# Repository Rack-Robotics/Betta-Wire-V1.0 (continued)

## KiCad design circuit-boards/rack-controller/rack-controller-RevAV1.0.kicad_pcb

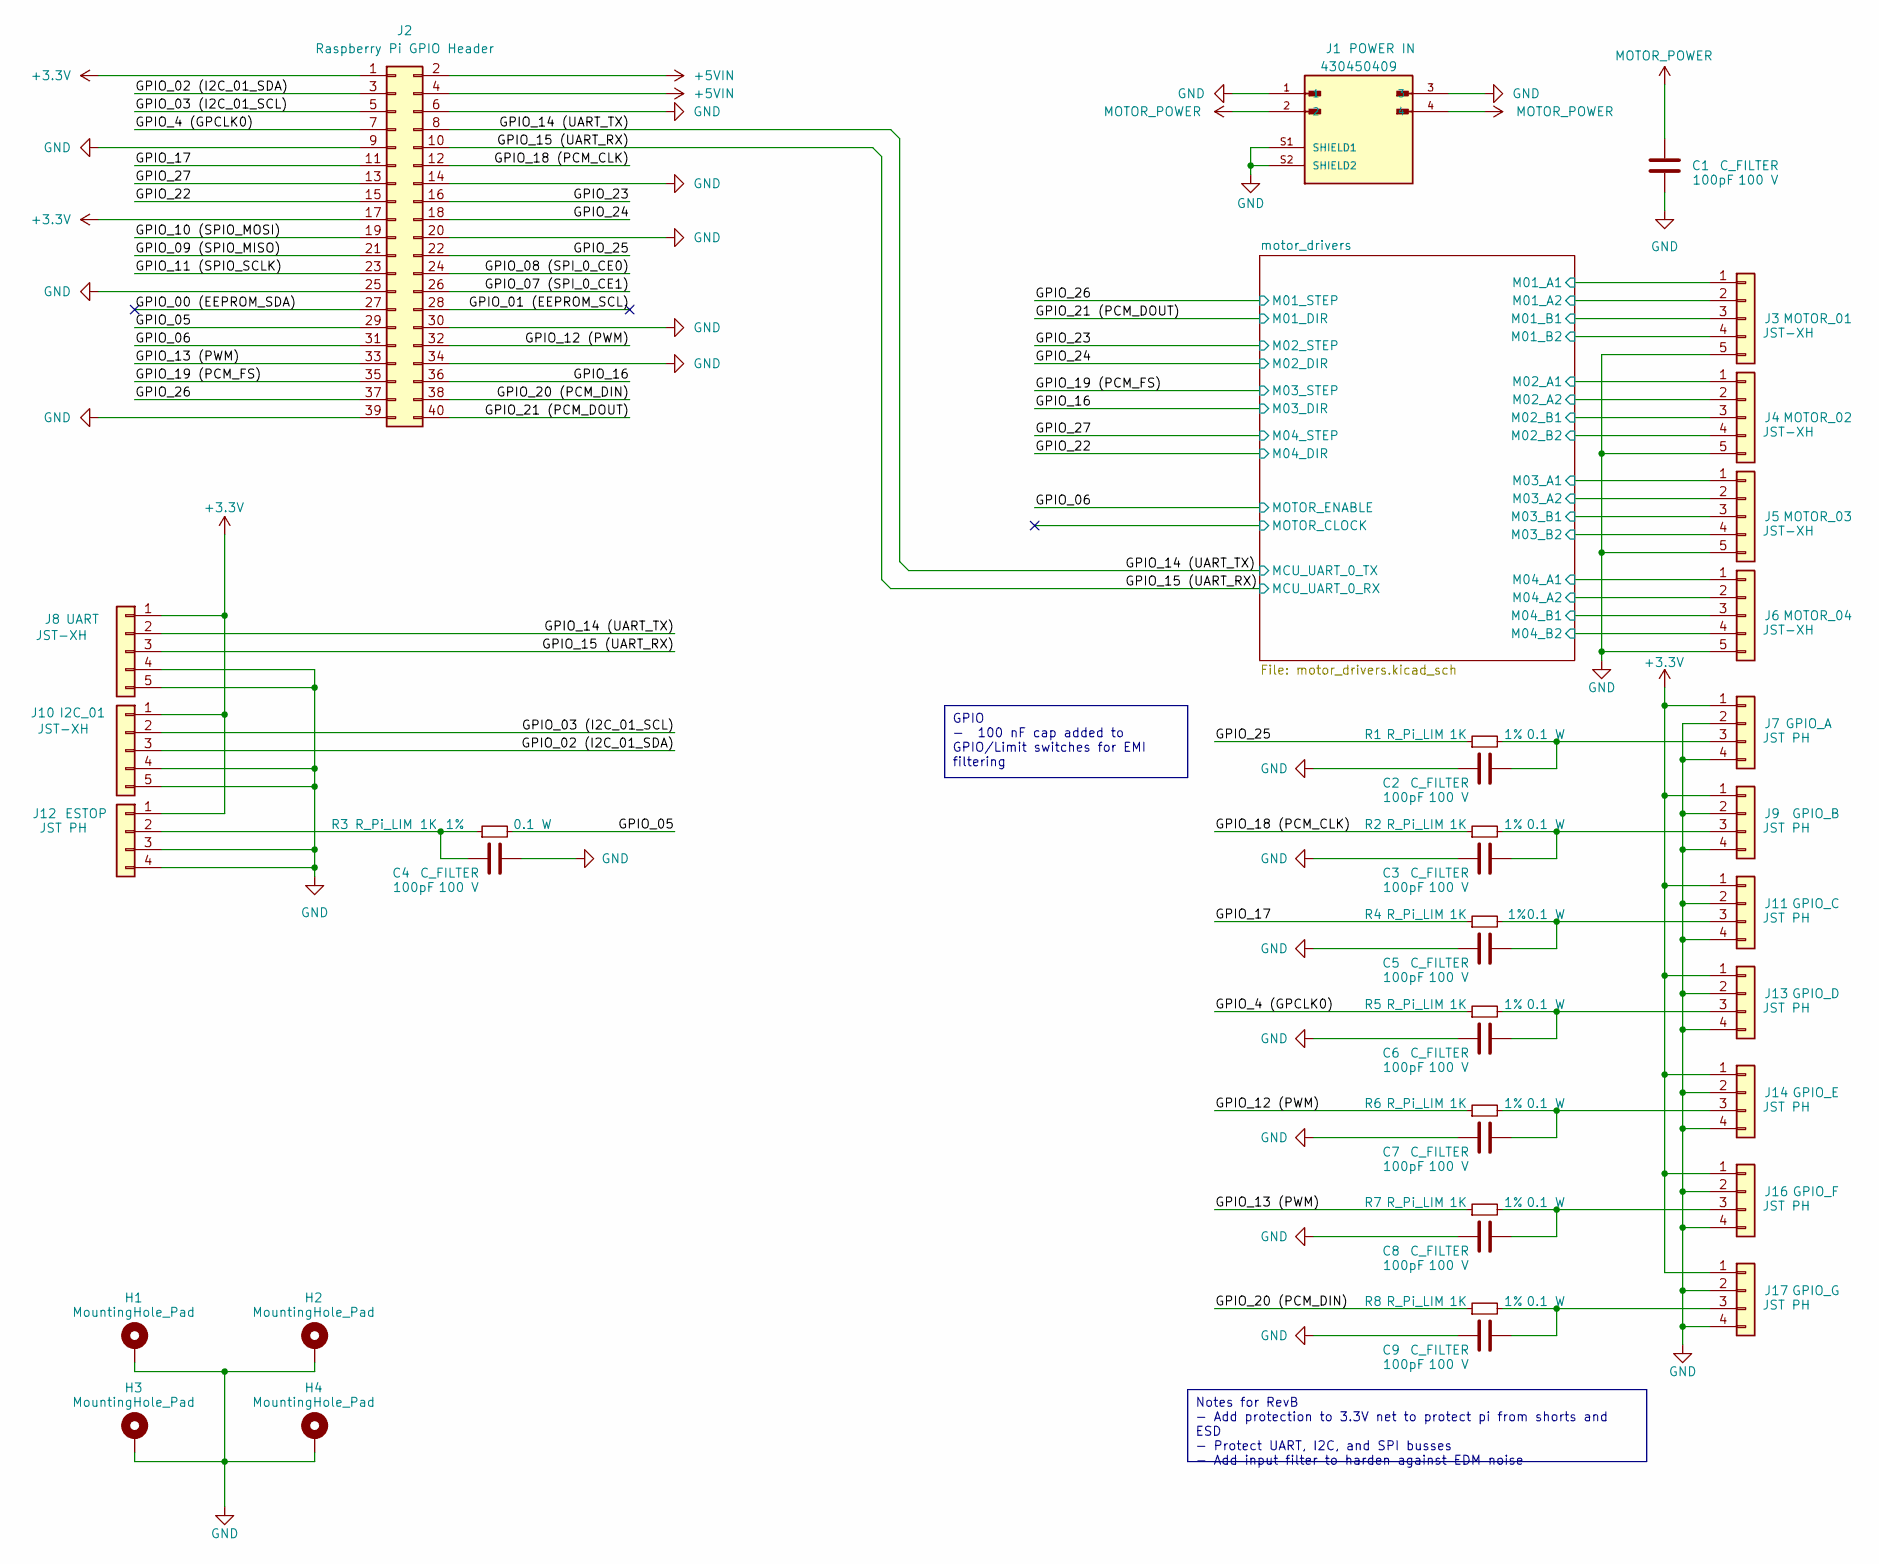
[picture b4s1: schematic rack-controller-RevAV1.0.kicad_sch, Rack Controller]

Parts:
C1, C2, C3, C4, C5, C6, C7, C8, C9: 100pF; C_0402_1005Metric; Voltage 100 V; Manufacturer# CC0402JRNPO0BN101; LCSC# C576700
H1, H2, H3, H4: MountingHole_Pad; MountingHole_3.2mm_M3_DIN965_Pad; Manufacturer# NULL; LCSC# NULL
J1: 430450409; MOLEX_430450409; Manufacturer# 0430450409; LCSC# C30602379
J2: Raspberry Pi GPIO Header; raspberrypi; Manufacturer# ESQ-120-23-T-D; LCSC# NULL
J3, J4, J5, J6, J8, J10: JST-XH; JST_XH_S4B-XH-SM4-TB_1x04-1MP_P2.50mm_Horizontal_custom; Manufacturer# S4B-XH-SM4-TB; LCSC# C161861
J7, J9, J11, J12, J13, J14, J16, J17: JST PH; JST_PH_S3B-PH-SM4-TB_1x03-1MP_P2.00mm_Horizontal_custom; Manufacturer# S3B-PH-SM4-TB; LCSC# C265101
R1, R2, R3, R4, R5, R6, R7, R8: 1K; R_0603_1608Metric; Tolerance 1%; Manufacturer# RC0603FR-071KL; LCSC# C22548

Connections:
+3.3V: J2.1, J2.17, J7.1, J8.1, J9.1, J10.1, J11.1, J12.1, J13.1, J14.1, J16.1, J17.1
+5VIN: J2.2, J2.4
/GPIO_00 (EEPROM_SDA): J2.27
/GPIO_01 (EEPROM_SCL): J2.28
/GPIO_02 (I2C_01_SDA): J2.3, J10.3
/GPIO_03 (I2C_01_SCL): J2.5, J10.2
/GPIO_4 (GPCLK0): J2.7, R5.1
/GPIO_05: J2.29, R3.2
/GPIO_06: J2.31; also elsewhere on the board
/GPIO_07 (SPI_0_CE1): J2.26
/GPIO_08 (SPI_0_CE0): J2.24
/GPIO_09 (SPIO_MISO): J2.21
/GPIO_10 (SPIO_MOSI): J2.19
/GPIO_11 (SPIO_SCLK): J2.23
/GPIO_12 (PWM): J2.32, R6.1
/GPIO_13 (PWM): J2.33, R7.1
/GPIO_14 (UART_TX): J2.8, J8.2; also elsewhere on the board
/GPIO_15 (UART_RX): J2.10, J8.3; also elsewhere on the board
/GPIO_16: J2.36; also elsewhere on the board
/GPIO_17: J2.11, R4.1
/GPIO_18 (PCM_CLK): J2.12, R2.1
/GPIO_19 (PCM_FS): J2.35; also elsewhere on the board
/GPIO_20 (PCM_DIN): J2.38, R8.1
/GPIO_21 (PCM_DOUT): J2.40; also elsewhere on the board
/GPIO_22: J2.15; also elsewhere on the board
/GPIO_23: J2.16; also elsewhere on the board
/GPIO_24: J2.18; also elsewhere on the board
/GPIO_25: J2.22, R1.1
/GPIO_26: J2.37; also elsewhere on the board
/GPIO_27: J2.13; also elsewhere on the board
/motor_drivers/M01_A1: J3.1; also elsewhere on the board
/motor_drivers/M01_A2: J3.2; also elsewhere on the board
/motor_drivers/M01_B1: J3.3; also elsewhere on the board
/motor_drivers/M01_B2: J3.4; also elsewhere on the board
/motor_drivers/M02_A1: J4.1; also elsewhere on the board
/motor_drivers/M02_A2: J4.2; also elsewhere on the board
/motor_drivers/M02_B1: J4.3; also elsewhere on the board
/motor_drivers/M02_B2: J4.4; also elsewhere on the board
/motor_drivers/M03_A1: J5.1; also elsewhere on the board
/motor_drivers/M03_A2: J5.2; also elsewhere on the board
/motor_drivers/M03_B1: J5.3; also elsewhere on the board
/motor_drivers/M03_B2: J5.4; also elsewhere on the board
/motor_drivers/M04_A1: J6.1; also elsewhere on the board
/motor_drivers/M04_A2: J6.2; also elsewhere on the board
/motor_drivers/M04_B1: J6.3; also elsewhere on the board
/motor_drivers/M04_B2: J6.4; also elsewhere on the board
GND: C1.1, C2.1, C3.1, C4.2, C5.1, C6.1, C7.1, C8.1, C9.1, H1.1, H2.1, H3.1, H4.1, J1.1, J1.3, J1.S1 (SHIELD1), J1.S2 (SHIELD2), J2.6, J2.9, J2.14, J2.20, J2.25, J2.30, J2.34, J2.39, J3.5, J4.5, J5.5, J6.5, J7.2, J7.4, J8.4, J8.5, J9.2, J9.4, J10.4, J10.5, J11.2, J11.4, J12.3, J12.4, J13.2, J13.4, J14.2, J14.4, J16.2, J16.4, J17.2, J17.4; also elsewhere on the board
MOTOR_POWER: C1.2, J1.2, J1.4; also elsewhere on the board
unnamed: C2.2, J7.3, R1.2
unnamed: C3.2, J9.3, R2.2
unnamed: C5.2, J11.3, R4.2
unnamed: C4.1, J12.2, R3.1
unnamed: C6.2, J13.3, R5.2
unnamed: C7.2, J14.3, R6.2
unnamed: C8.2, J16.3, R7.2
unnamed: C9.2, J17.3, R8.2

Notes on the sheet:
GPIO - 100 nF cap added to GPIO/Limit switches for EMI filtering
Notes for RevB - Add protection to 3.3V net to protect pi from shorts and ESD - Protect UART, I2C, and SPI busses - Add input filter to harden against EDM noise

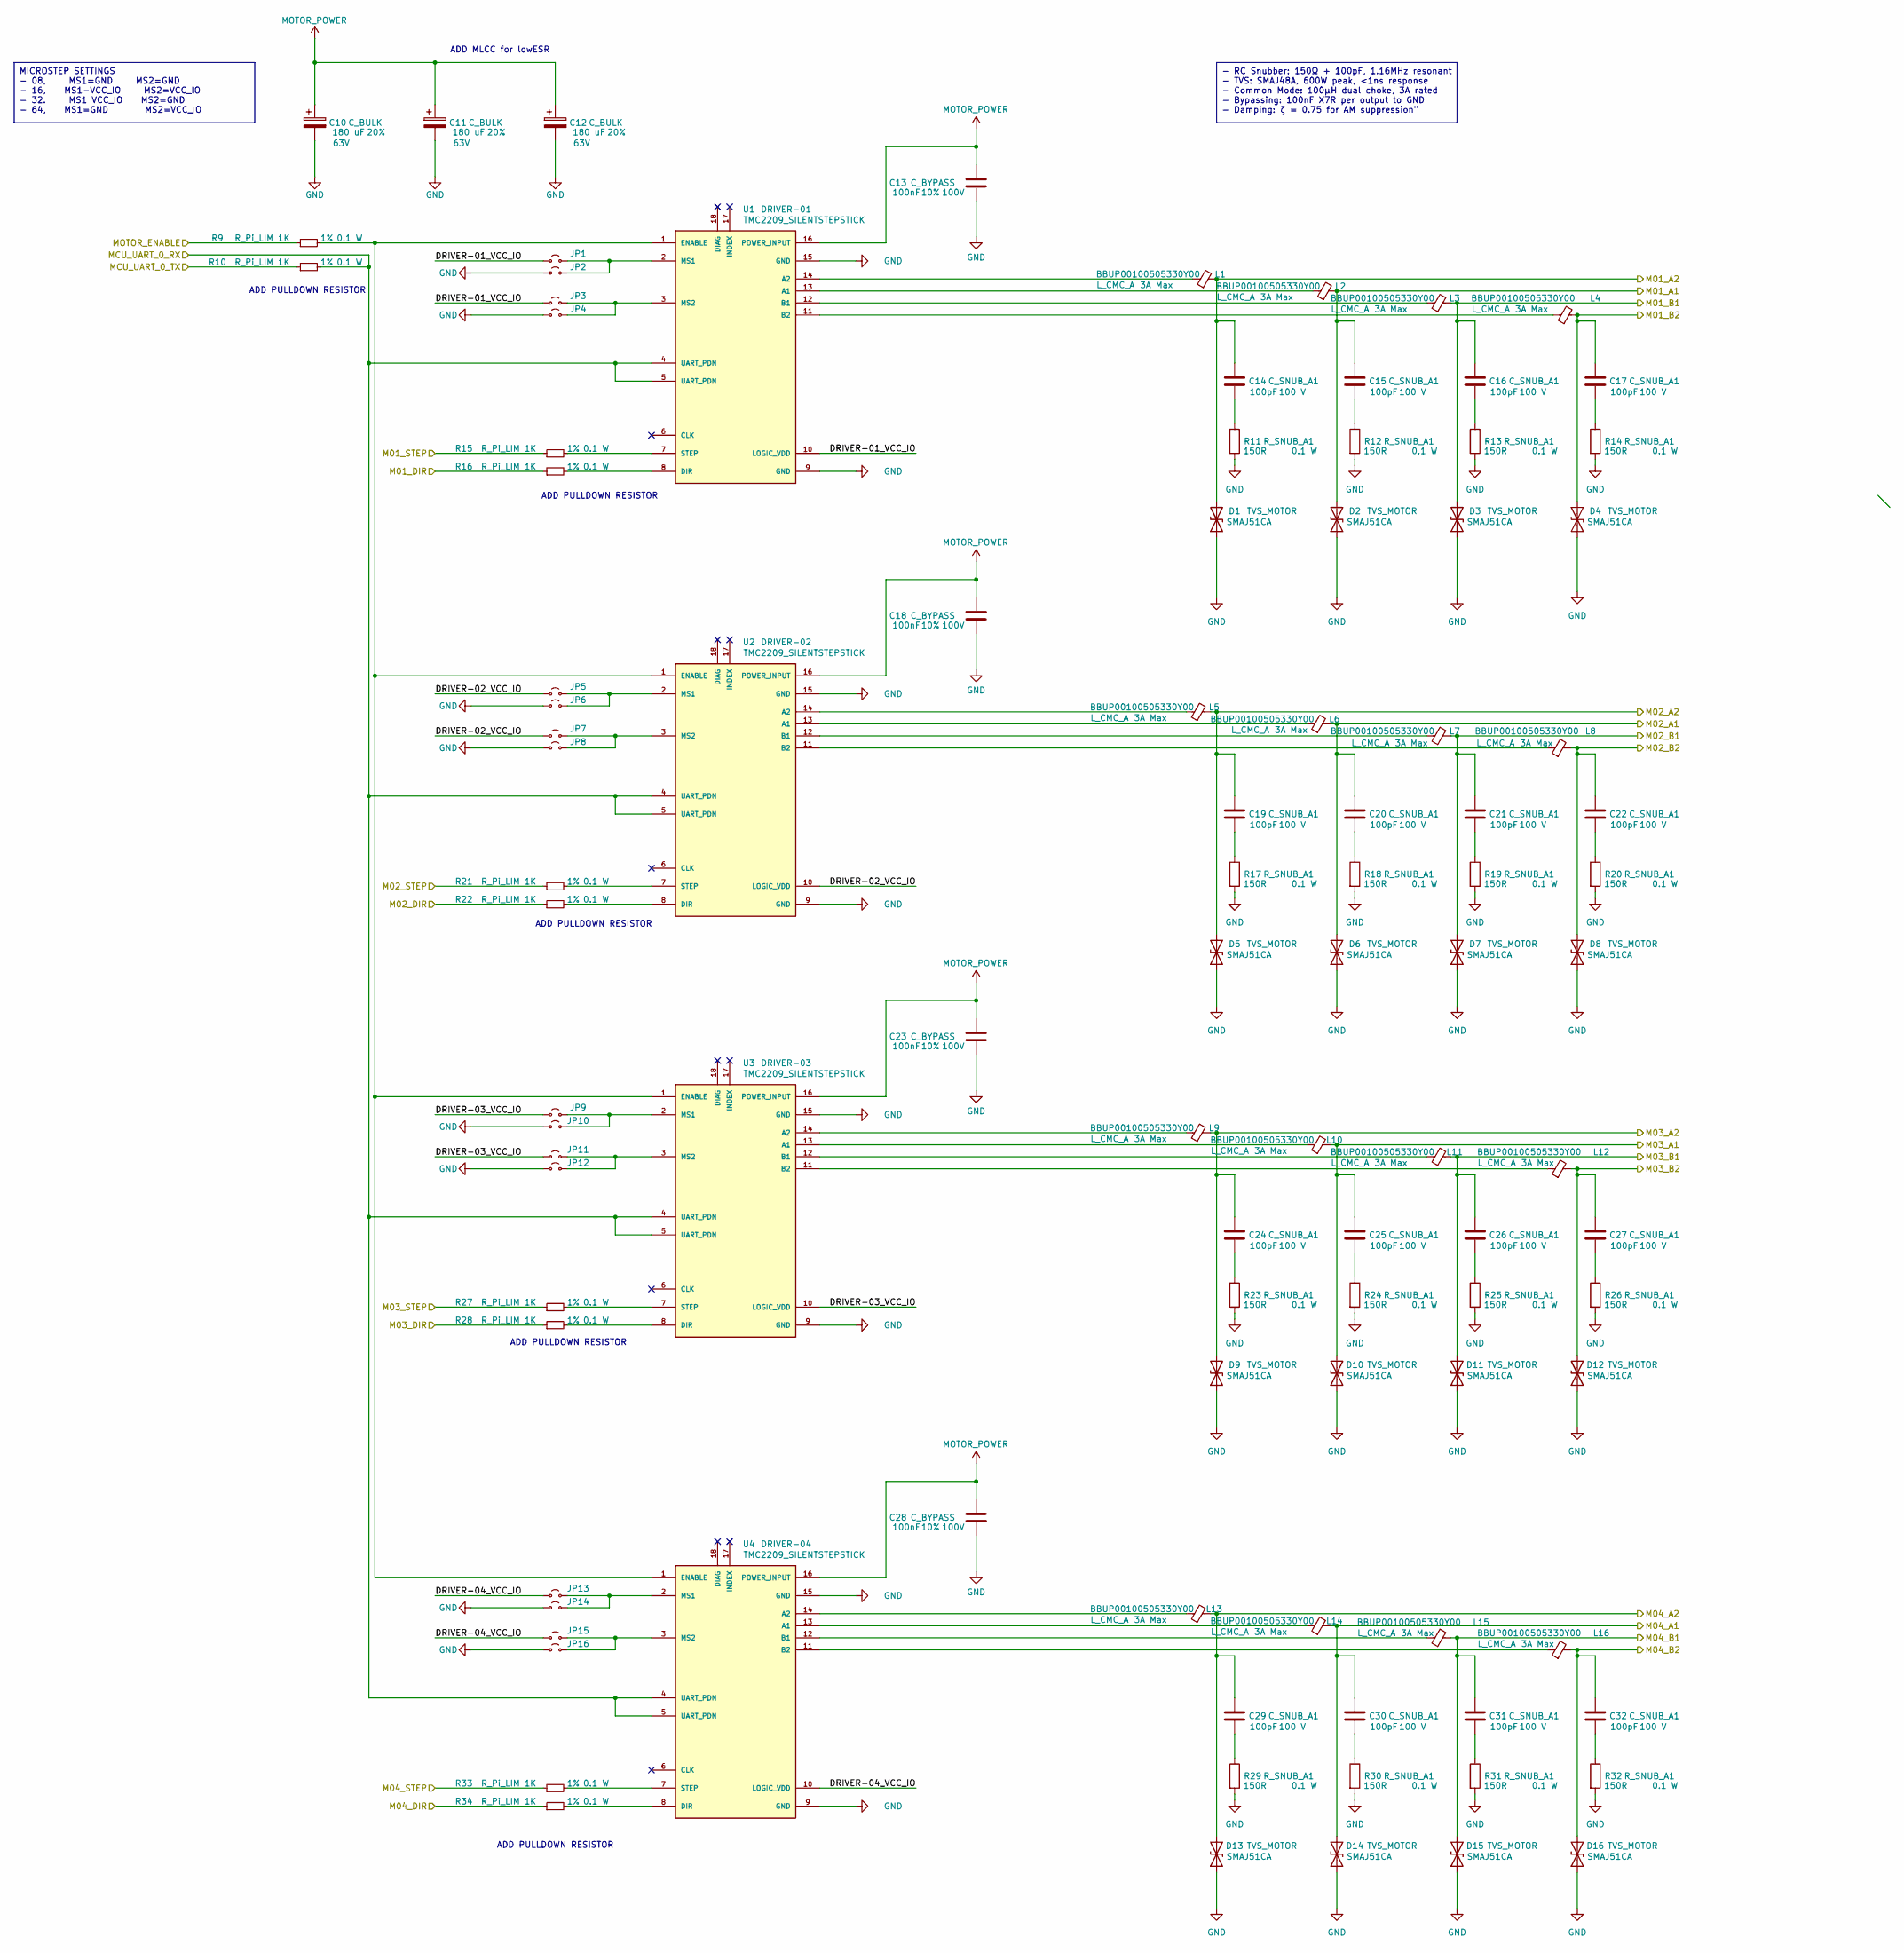
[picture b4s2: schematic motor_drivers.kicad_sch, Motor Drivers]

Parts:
C10, C11, C12: 180 uF; CP_Elec_10x10; Voltage 63V; Tolerance 20%; Manufacturer# A785MW187M1JLAS013; LCSC# NULL
C13, C18, C23, C28: 100nF; C_0603_1608Metric; Voltage 100V; Tolerance 10%; Manufacturer# CC0603KRX7R0BB104; LCSC# C113803
C14, C15, C16, C17, C19, C20, C21, C22, C24, C25, C26, C27, C29, C30, C31, C32: 100pF; C_0402_1005Metric; Voltage 100 V; Manufacturer# CC0402JRNPO0BN101; LCSC# C576700
D1, D2, D3, D4, D5, D6, D7, D8, D9, D10, D11, D12, D13, D14, D15, D16: SMAJ51CA; D_SMA; Manufacturer# SMAJ60CA-13-F; LCSC# C135003
JP1, JP2, JP3, JP4, JP5, JP6, JP7, JP8, JP9, JP10, JP11, JP12, JP13, JP14, JP15, JP16: NULL; SolderJumper-2_P1mm_UnBridged_Pad1.6x1.6mm; Manufacturer# NULL; LCSC# NULL
L1, L2, L3, L4, L5, L6, L7, L8, L9, L10, L11, L12, L13, L14, L15, L16: BBUP00100505330Y00; L_0402_1005Metric; Manufacturer# BLM15AX100SN1D; LCSC# C668299
R9, R10, R15, R16, R21, R22, R27, R28, R33, R34: 1K; R_0603_1608Metric; Tolerance 1%; Manufacturer# RC0603FR-071KL; LCSC# C22548
R11, R12, R13, R14, R17, R18, R19, R20, R23, R24, R25, R26, R29, R30, R31, R32: 150R; R_0603_1608Metric; Tolerance 1%; Manufacturer# RC0603FR-07150RL; LCSC# C114608
U1, U2, U3, U4: TMC2209_SILENTSTEPSTICK; BTT_TMC2209_V1.3; Manufacturer# TMC2209_V1.3; LCSC# NULL

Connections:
/GPIO_06: R9.1; also elsewhere on the board
/GPIO_14 (UART_TX): R10.1; also elsewhere on the board
/GPIO_15 (UART_RX): R10.2, U1.4 (UART_PDN), U1.5 (UART_PDN), U2.4 (UART_PDN), U2.5 (UART_PDN), U3.4 (UART_PDN), U3.5 (UART_PDN), U4.4 (UART_PDN), U4.5 (UART_PDN); also elsewhere on the board
/GPIO_16: R28.1; also elsewhere on the board
/GPIO_19 (PCM_FS): R27.1; also elsewhere on the board
/GPIO_21 (PCM_DOUT): R16.1; also elsewhere on the board
/GPIO_22: R34.1; also elsewhere on the board
/GPIO_23: R21.1; also elsewhere on the board
/GPIO_24: R22.1; also elsewhere on the board
/GPIO_26: R15.1; also elsewhere on the board
/GPIO_27: R33.1; also elsewhere on the board
/motor_drivers/DRIVER-01_VCC_IO: JP1.1 (A), JP3.1 (A), U1.10 (LOGIC_VDD)
/motor_drivers/DRIVER-02_VCC_IO: JP5.1 (A), JP7.1 (A), U2.10 (LOGIC_VDD)
/motor_drivers/DRIVER-03_VCC_IO: JP9.1 (A), JP11.1 (A), U3.10 (LOGIC_VDD)
/motor_drivers/DRIVER-04_VCC_IO: JP13.1 (A), JP15.1 (A), U4.10 (LOGIC_VDD)
/motor_drivers/M01_A1: C15.1, D2.2 (A2), L2.2; also elsewhere on the board
/motor_drivers/M01_A2: C14.1, D1.2 (A2), L1.2; also elsewhere on the board
/motor_drivers/M01_B1: C16.1, D3.2 (A2), L3.2; also elsewhere on the board
/motor_drivers/M01_B2: C17.1, D4.2 (A2), L4.2; also elsewhere on the board
/motor_drivers/M02_A1: C20.1, D6.2 (A2), L6.2; also elsewhere on the board
/motor_drivers/M02_A2: C19.1, D5.2 (A2), L5.2; also elsewhere on the board
/motor_drivers/M02_B1: C21.1, D7.2 (A2), L7.2; also elsewhere on the board
/motor_drivers/M02_B2: C22.1, D8.2 (A2), L8.2; also elsewhere on the board
/motor_drivers/M03_A1: C25.1, D10.2 (A2), L10.2; also elsewhere on the board
/motor_drivers/M03_A2: C24.1, D9.2 (A2), L9.2; also elsewhere on the board
/motor_drivers/M03_B1: C26.1, D11.2 (A2), L11.2; also elsewhere on the board
/motor_drivers/M03_B2: C27.1, D12.2 (A2), L12.2; also elsewhere on the board
/motor_drivers/M04_A1: C30.1, D14.2 (A2), L14.2; also elsewhere on the board
/motor_drivers/M04_A2: C29.1, D13.2 (A2), L13.2; also elsewhere on the board
/motor_drivers/M04_B1: C31.1, D15.2 (A2), L15.2; also elsewhere on the board
/motor_drivers/M04_B2: C32.1, D16.2 (A2), L16.2; also elsewhere on the board
GND: C10.2, C11.2, C12.2, C13.2, C18.2, C23.2, C28.2, D1.1 (A1), D2.1 (A1), D3.1 (A1), D4.1 (A1), D5.1 (A1), D6.1 (A1), D7.1 (A1), D8.1 (A1), D9.1 (A1), D10.1 (A1), D11.1 (A1), D12.1 (A1), D13.1 (A1), D14.1 (A1), D15.1 (A1), D16.1 (A1), JP2.1 (A), JP4.1 (A), JP6.1 (A), JP8.1 (A), JP10.1 (A), JP12.1 (A), JP14.1 (A), JP16.1 (A), R11.2, R12.2, R13.2, R14.2, R17.2, R18.2, R19.2, R20.2, R23.2, R24.2, R25.2, R26.2, R29.2, R30.2, R31.2, R32.2, U1.9 (GND), U1.15 (GND), U2.9 (GND), U2.15 (GND), U3.9 (GND), U3.15 (GND), U4.9 (GND), U4.15 (GND); also elsewhere on the board
MOTOR_POWER: C10.1, C11.1, C12.1, C13.1, C18.1, C23.1, C28.1, U1.16 (POWER_INPUT), U2.16 (POWER_INPUT), U3.16 (POWER_INPUT), U4.16 (POWER_INPUT); also elsewhere on the board
unnamed: C14.2, R11.1
unnamed: C15.2, R12.1
unnamed: C16.2, R13.1
unnamed: C17.2, R14.1
unnamed: C19.2, R17.1
unnamed: C20.2, R18.1
unnamed: C21.2, R19.1
unnamed: C22.2, R20.1
unnamed: C24.2, R23.1
unnamed: C25.2, R24.1
unnamed: C26.2, R25.1
unnamed: C27.2, R26.1
unnamed: C29.2, R29.1
unnamed: C30.2, R30.1
unnamed: C31.2, R31.1
unnamed: C32.2, R32.1
unnamed: JP1.2 (B), JP2.2 (B), U1.2 (MS1)
unnamed: JP3.2 (B), JP4.2 (B), U1.3 (MS2)
unnamed: JP5.2 (B), JP6.2 (B), U2.2 (MS1)
unnamed: JP7.2 (B), JP8.2 (B), U2.3 (MS2)
unnamed: JP9.2 (B), JP10.2 (B), U3.2 (MS1)
unnamed: JP11.2 (B), JP12.2 (B), U3.3 (MS2)
unnamed: JP13.2 (B), JP14.2 (B), U4.2 (MS1)
unnamed: JP15.2 (B), JP16.2 (B), U4.3 (MS2)
unnamed: L2.1, U1.13 (A1)
unnamed: L1.1, U1.14 (A2)
unnamed: L3.1, U1.12 (B1)
unnamed: L4.1, U1.11 (B2)
unnamed: R16.2, U1.8 (DIR)
unnamed: R9.2, U1.1 (ENABLE), U2.1 (ENABLE), U3.1 (ENABLE), U4.1 (ENABLE)
unnamed: R15.2, U1.7 (STEP)
unnamed: L6.1, U2.13 (A1)
unnamed: L5.1, U2.14 (A2)
unnamed: L7.1, U2.12 (B1)
unnamed: L8.1, U2.11 (B2)
unnamed: R22.2, U2.8 (DIR)
unnamed: R21.2, U2.7 (STEP)
unnamed: L10.1, U3.13 (A1)
unnamed: L9.1, U3.14 (A2)
unnamed: L11.1, U3.12 (B1)
unnamed: L12.1, U3.11 (B2)
unnamed: R28.2, U3.8 (DIR)
unnamed: R27.2, U3.7 (STEP)
unnamed: L14.1, U4.13 (A1)
unnamed: L13.1, U4.14 (A2)
unnamed: L15.1, U4.12 (B1)
unnamed: L16.1, U4.11 (B2)
unnamed: R34.2, U4.8 (DIR)
unnamed: R33.2, U4.7 (STEP)

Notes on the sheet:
- RC Snubber: 150Ω + 100pF, 1.16MHz resonant - TVS: SMAJ48A, 600W peak, <1ns response - Common Mode: 100µH dual choke, 3A rated - Bypassing: 100nF X7R per output to GND - Damping: ζ = 0.75 for AM suppression"
MICROSTEP SETTINGS - 08, MS1=GND MS2=GND - 16, MS1-VCC_IO MS2=VCC_IO - 32. MS1 VCC_IO MS2=GND - 64, MS1=GND MS2=VCC_IO
ADD PULLDOWN RESISTOR
ADD MLCC for lowESR

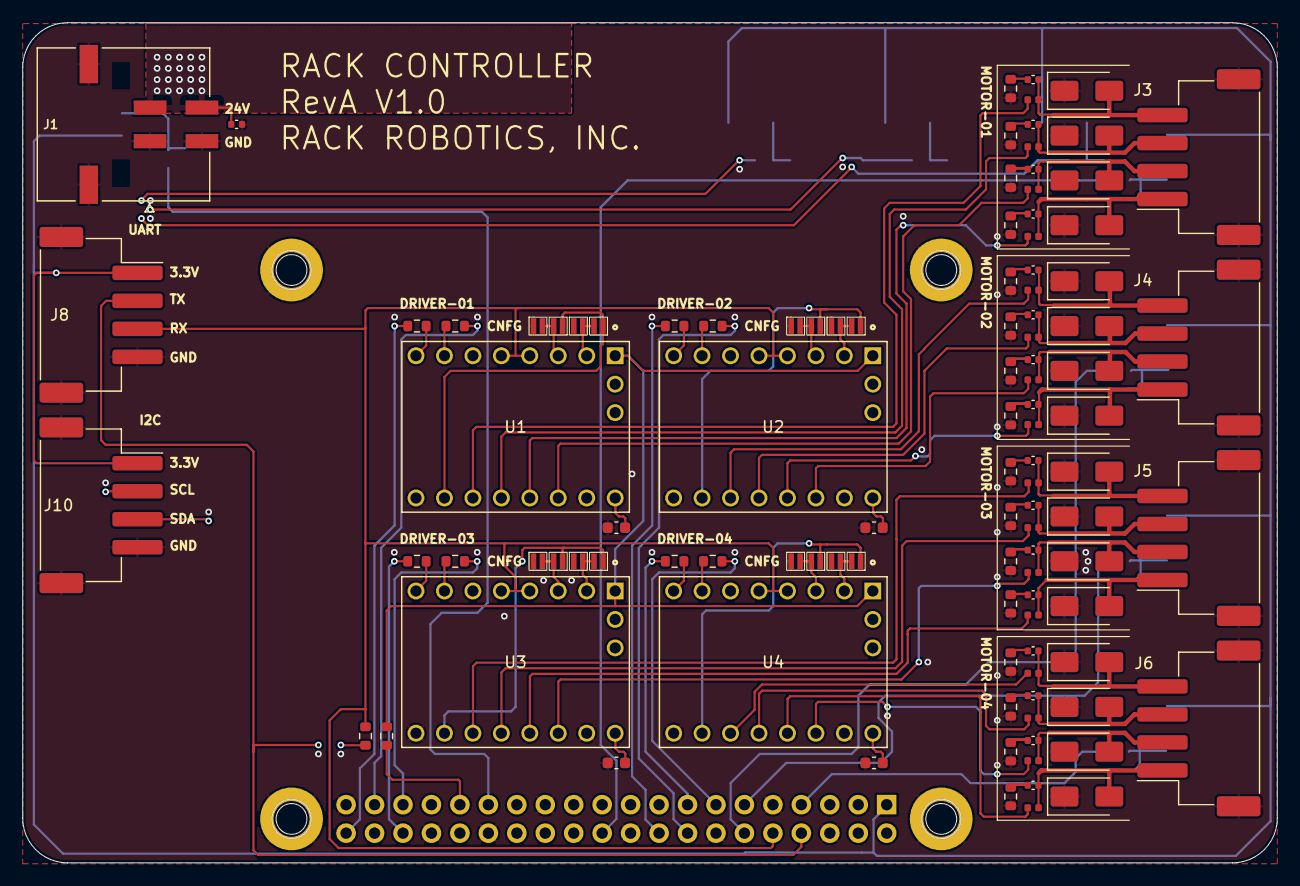
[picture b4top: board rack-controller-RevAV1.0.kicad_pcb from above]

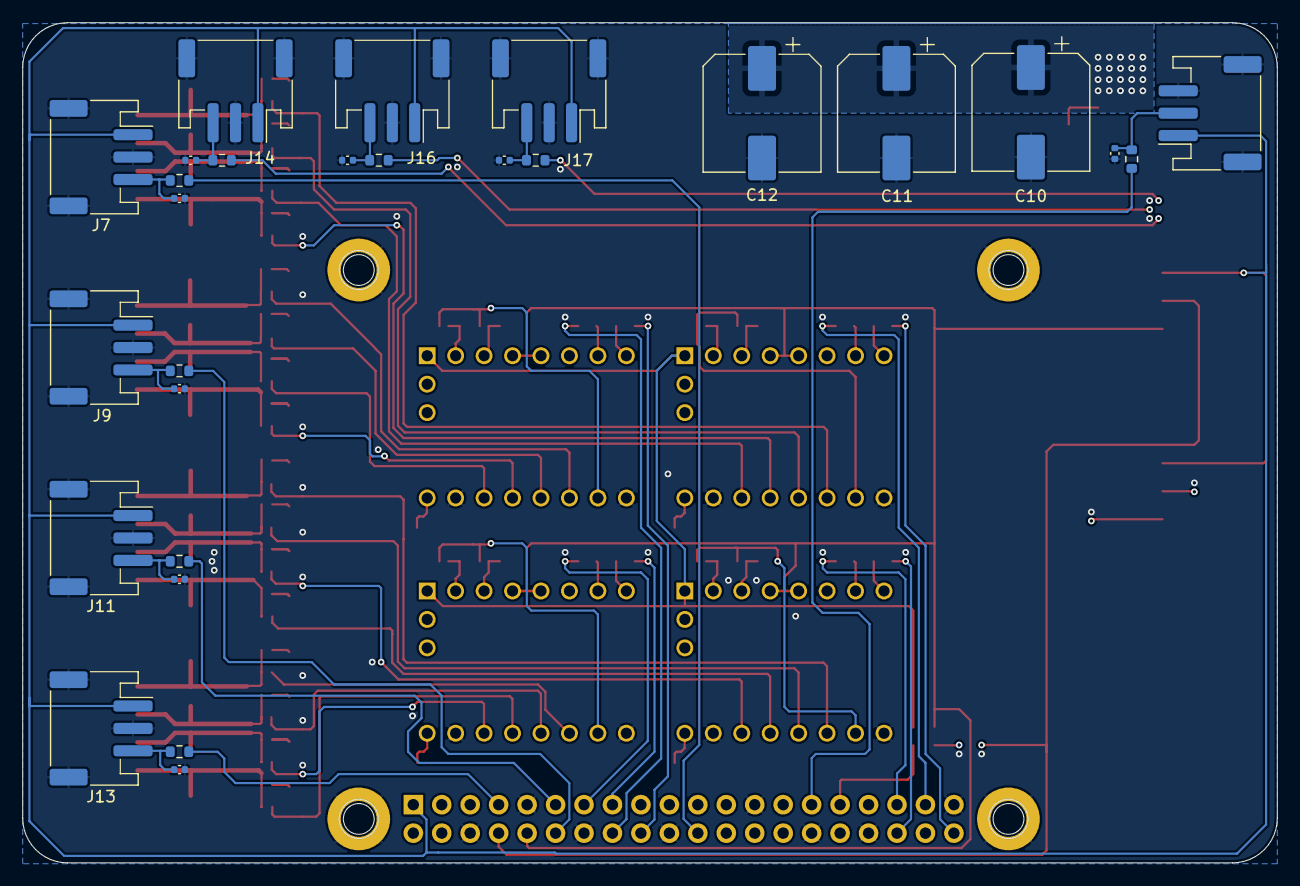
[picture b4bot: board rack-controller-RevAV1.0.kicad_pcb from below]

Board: 6 copper layers, 112.0 x 75.0 mm, 139 parts (27 on the bottom side), 102 nets.

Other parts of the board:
RP4: Raspberry_Pi; raspberrypi-outline

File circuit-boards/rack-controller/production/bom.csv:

Designator,Footprint,Quantity,Value,LCSC Part #
"C1, C14, C15, C16, C17, C19, C2, C20, C21, C22, C24, C25, C26, C27, C29, C3, C30, C31, C32, C4, C5, C6, C7, C8, C9",0402,25,100pF,
"C10, C11, C12",CP_Elec_10x10,3,180 uF,
"C13, C18, C23, C28",0603,4,100nF,
"D1, D10, D11, D12, D13, D14, D15, D16, D2, D3, D4, D5, D6, D7, D8, D9",D_SMA,16,SMAJ51CA,
J1,MOLEX_430450409,1,430450409,
"J10, J3, J4, J5, J6, J8",JST_XH_S4B-XH-SM4-TB_1x04-1MP_P2.50mm_Horizontal_custom,6,JST-XH,
"J11, J12, J13, J14, J16, J17, J7, J9",JST_PH_S3B-PH-SM4-TB_1x03-1MP_P2.00mm_Horizontal_custom,8,JST PH,
J2,raspberrypi,1,Raspberry Pi GPIO Header,
"JP1, JP10, JP11, JP12, JP13, JP14, JP15, JP16, JP2, JP3, JP4, JP5, JP6, JP7, JP8, JP9",SolderJumper-2_P1mm_UnBridged_Pad1.6x1.6mm,16,NULL,
"L1, L10, L11, L12, L13, L14, L15, L16, L2, L3, L4, L5, L6, L7, L8, L9",0402,16,BBUP00100505330Y00,
"R1, R10, R15, R16, R2, R21, R22, R27, R28, R3, R33, R34, R4, R5, R6, R7, R8, R9",0603,18,1K,
"R11, R12, R13, R14, R17, R18, R19, R20, R23, R24, R25, R26, R29, R30, R31, R32",0603,16,150R,
"U1, U2, U3, U4",BTT_TMC2209_V1.3,4,TMC2209_SILENTSTEPSTICK,

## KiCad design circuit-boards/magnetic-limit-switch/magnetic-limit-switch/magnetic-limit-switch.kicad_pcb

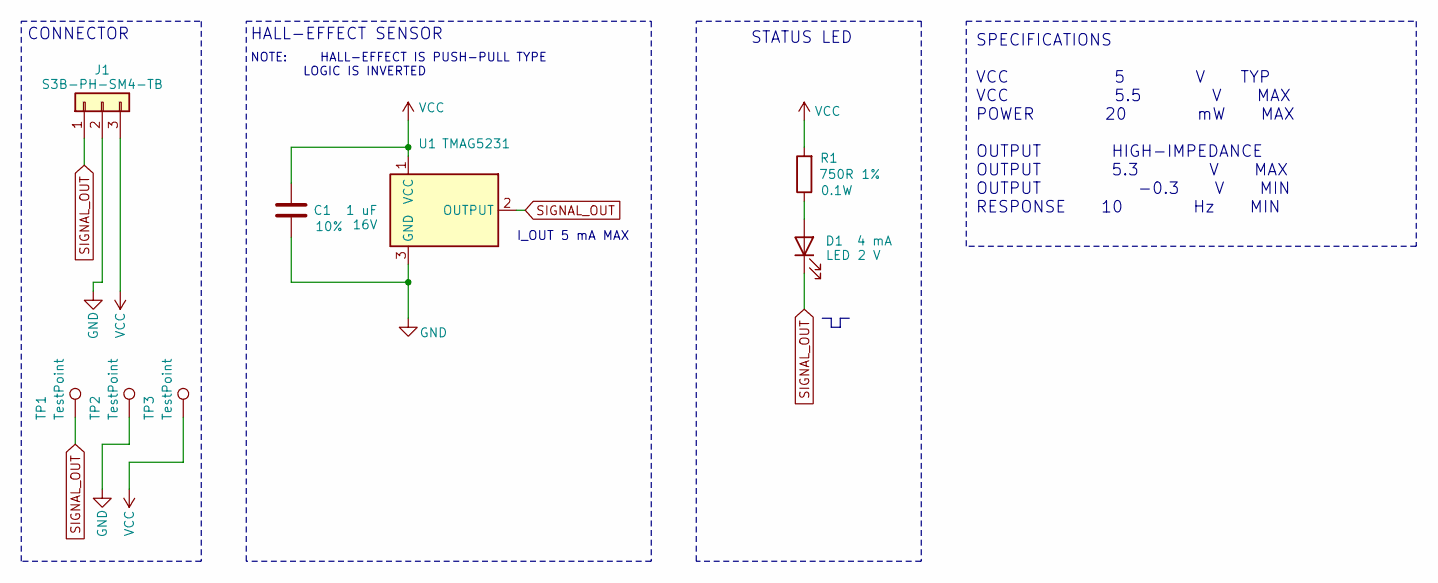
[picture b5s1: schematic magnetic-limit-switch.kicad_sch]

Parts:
C1: 1 uF; C_0603_1608Metric; Tolerance 10%; Manufacterer# CC0603KRX7R7BB105; LCSC Part # C106248
D1: LED; LED_0603_1608Metric; Manufacterer# LTST-C193KFKT-5A; LCSC Part # C284922
J1: S3B-PH-SM4-TB; JST_PH_S3B-PH-SM4-TB_1x03-1MP_P2.00mm_Horizontal; Manufacterer# S3B-PH-SM4-TB; LCSC Part # NULL
R1: 750R; R_0603_1608Metric; Tolerance 1%; Manufacterer# RC0603FR-07750RL; LCSC Part # C114635
TP1, TP2, TP3: TestPoint; TestPoint_Pad_1.0x1.0mm; Manufacterer# NULL; LCSC Part # NULL
U1: TMAG5231; SOT-23-3; Manufacterer# TMAG5231A2DQDBZR; LCSC Part # NULL

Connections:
GND: C1.1, J1.2, TP2.1, U1.3 (GND)
unnamed: D1.2 (A), R1.1
SIGNAL_OUT: D1.1 (K), J1.1, TP1.1, U1.2 (OUTPUT)
VCC: C1.2, J1.3, R1.2, TP3.1, U1.1 (VCC)

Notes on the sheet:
NOTE: HALL-EFFECT IS PUSH-PULL TYPE LOGIC IS INVERTED
CONNECTOR
HALL-EFFECT SENSOR
STATUS LED
SPECIFICATIONS VCC 5 V TYP VCC 5.5 V MAX POWER 20 mW MAX OUTPUT HIGH-IMPEDANCE OUTPUT 5.3 V MAX OUTPUT -0.3 V MIN RESPONSE 10 Hz MIN
I_OUT 5 mA MAX

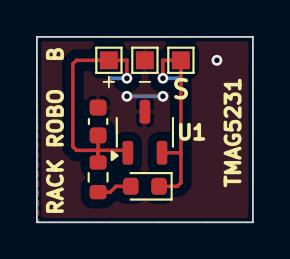
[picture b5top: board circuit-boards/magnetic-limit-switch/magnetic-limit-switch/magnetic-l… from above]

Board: 2 copper layers, 12.0 x 10.3 mm, 8 parts (1 on the bottom side), 4 nets.

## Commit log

2024-06-03 Update README.md license
2024-06-03 uploaded license
2024-06-03 added CAD, firmware, & images
2024-06-03 added image of tools
2024-06-03 added images of motor banks and e-box
2024-06-04 removed RevA files from RevB fork, modified designdecisions.md
2024-06-16 improved design decisions
2024-06-26 added requirements doc
2024-06-26 updated requirements
2024-06-26 added requirements for closed-loop feedrate control
2024-06-26 fixed typo in requirements
2024-06-29 Update betta-wire-v1.0-revb-requirements.md with analog voltage
2024-08-02 updated wire EDM toolhead sections
2024-08-15 updated design decisions
2024-08-15 updated requirements and organized into folder
2024-08-19 updated requirements with wire tension specs
2024-08-21 IP68 limit switch
2024-08-21 updated constraints to 0.2 mm diameter wire
2024-10-21 Proofreading
    Cleaned up formatting. Fixed a few spelling errors. Removed a few unnecessary words. Added further description. Added a link where appropriate.
2024-10-21 Link fixes, typo fix, fastener update
    Made links point directly to portion of page being referenced. Removed "L" from "Stainless Steel 316L". Added first change to fastener requirements. Change to Torx head fasteners and a move away from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
2024-10-21 Hardware Section Update
    Updated fastener material. Extra information on fastener selection. Stressed pin selection. Made size requirements more clear while leaving them open. Typo fix.
    Added segment to aquarium sizing. Called out required minimum tank size. Called out common tank sizes likely to work well.
2024-10-21 Hardware Section Clarification
    Added brief description of ISO standards to remove need for encyclopedic knowledge of ISO standards or a GPT query.
2024-10-23 Clarified features. Added QoL section.
    Mentioned kinematic fixes and stainless steel use.
    Added QoL section. Outlined several important changes that improve user QoL.
2024-10-23 Addition to QoL Segment
    Added cable chain requirement.
2024-10-24 New QoL feature. Handles
    Handles for removal from aquarium
2025-01-17 RevB of Limit Switch
    - switched from TH JST-XH to SMD JST-PH
    - Minimized size down to volume of connector
    - added LCSC part numbers for JLCPCB assembly
2025-01-17 toolhead-rod-energized
    - SMD connectors with ring terminals
    - 6A 300VMAX
2025-01-19 file reorganization
2025-01-31 firmware for wire tool added
    - implemented wire velocity reporting over serial for prototype testing with AS5600 encoder
    - renamed electronics folder to circuit-boards
2025-01-31 Update wire-tool-firmware.ino
    - commands for all functions run properly
    - telemetry reporting added
    - emergency reset behavior added
2025-01-31 ready for PID loop implementation
2025-02-01 PID loop added for velocity
    PID loop functional, but not tuned
2025-02-01 Update wire-tool-firmware.ino
    implemented current sensing and motor driving for both top and bottom tools
2025-02-01 Update wire-tool-firmware.ino
    - implemented semi-automaic loading of wire
    - debugged current sensors
2025-02-12 added rack controller motherboard RevA
2025-02-13 schematic for control board revised
2025-02-13 updated 48V->5V buck to 3A
2025-02-18 Completed control board revB`
    - fixed UART bus
    - fixed pullup and pulldown resistors
    -layout completed for new board outline
2025-03-07 modified BoM & STEPs for export
2025-03-12 Removed Spring Conn Rod Energizer
2025-03-13 removed UART
2025-03-13 rack controller revC production files
    - Removed UART
    - Added resistors for microstep selection
    - Renamed connectors starting from index 0
    - Fixed Pi PSU GND error from RevB
    - Reduced layers from 6 to 4
2025-03-13 magnetic endstop revC
    - Changed connector to JST-XH, SMD version
    - 16 mm x 20 mm
    - Do-not-populate LED
2025-04-25 schematic for BDC motor drivers 00 and 01
2025-04-26 layout of revD
2025-05-05 Update README.md with new features
    Added assisted threading and hole popping as confirmed features along with short descriptions.
2025-05-11 re-exported STEP for motherboard
2025-05-31 N30 Motor Board
2025-07-27 updated text in schematic
2025-07-27 increased number of stitching vias for ground planes
2025-07-29 RevE of Rack Controller
    - Improved BDC drivers for I2C control
    - Removed aluminum polymer caps
    - Added fan vent hole
    - Rerouted
    - Added ferrites on BDC output
2025-08-20 magnetic endstop revD
    - improved silkscreen
    - DNP connector (solder to pads)
    - strain relief for wires
2025-11-17 Rack-Controller-Rev-F
    - 3 channel high-side power switches
    - 5 stepper motor driver sockets
    - 2 brushed dc motor drivers with selection between 24V and 9V
